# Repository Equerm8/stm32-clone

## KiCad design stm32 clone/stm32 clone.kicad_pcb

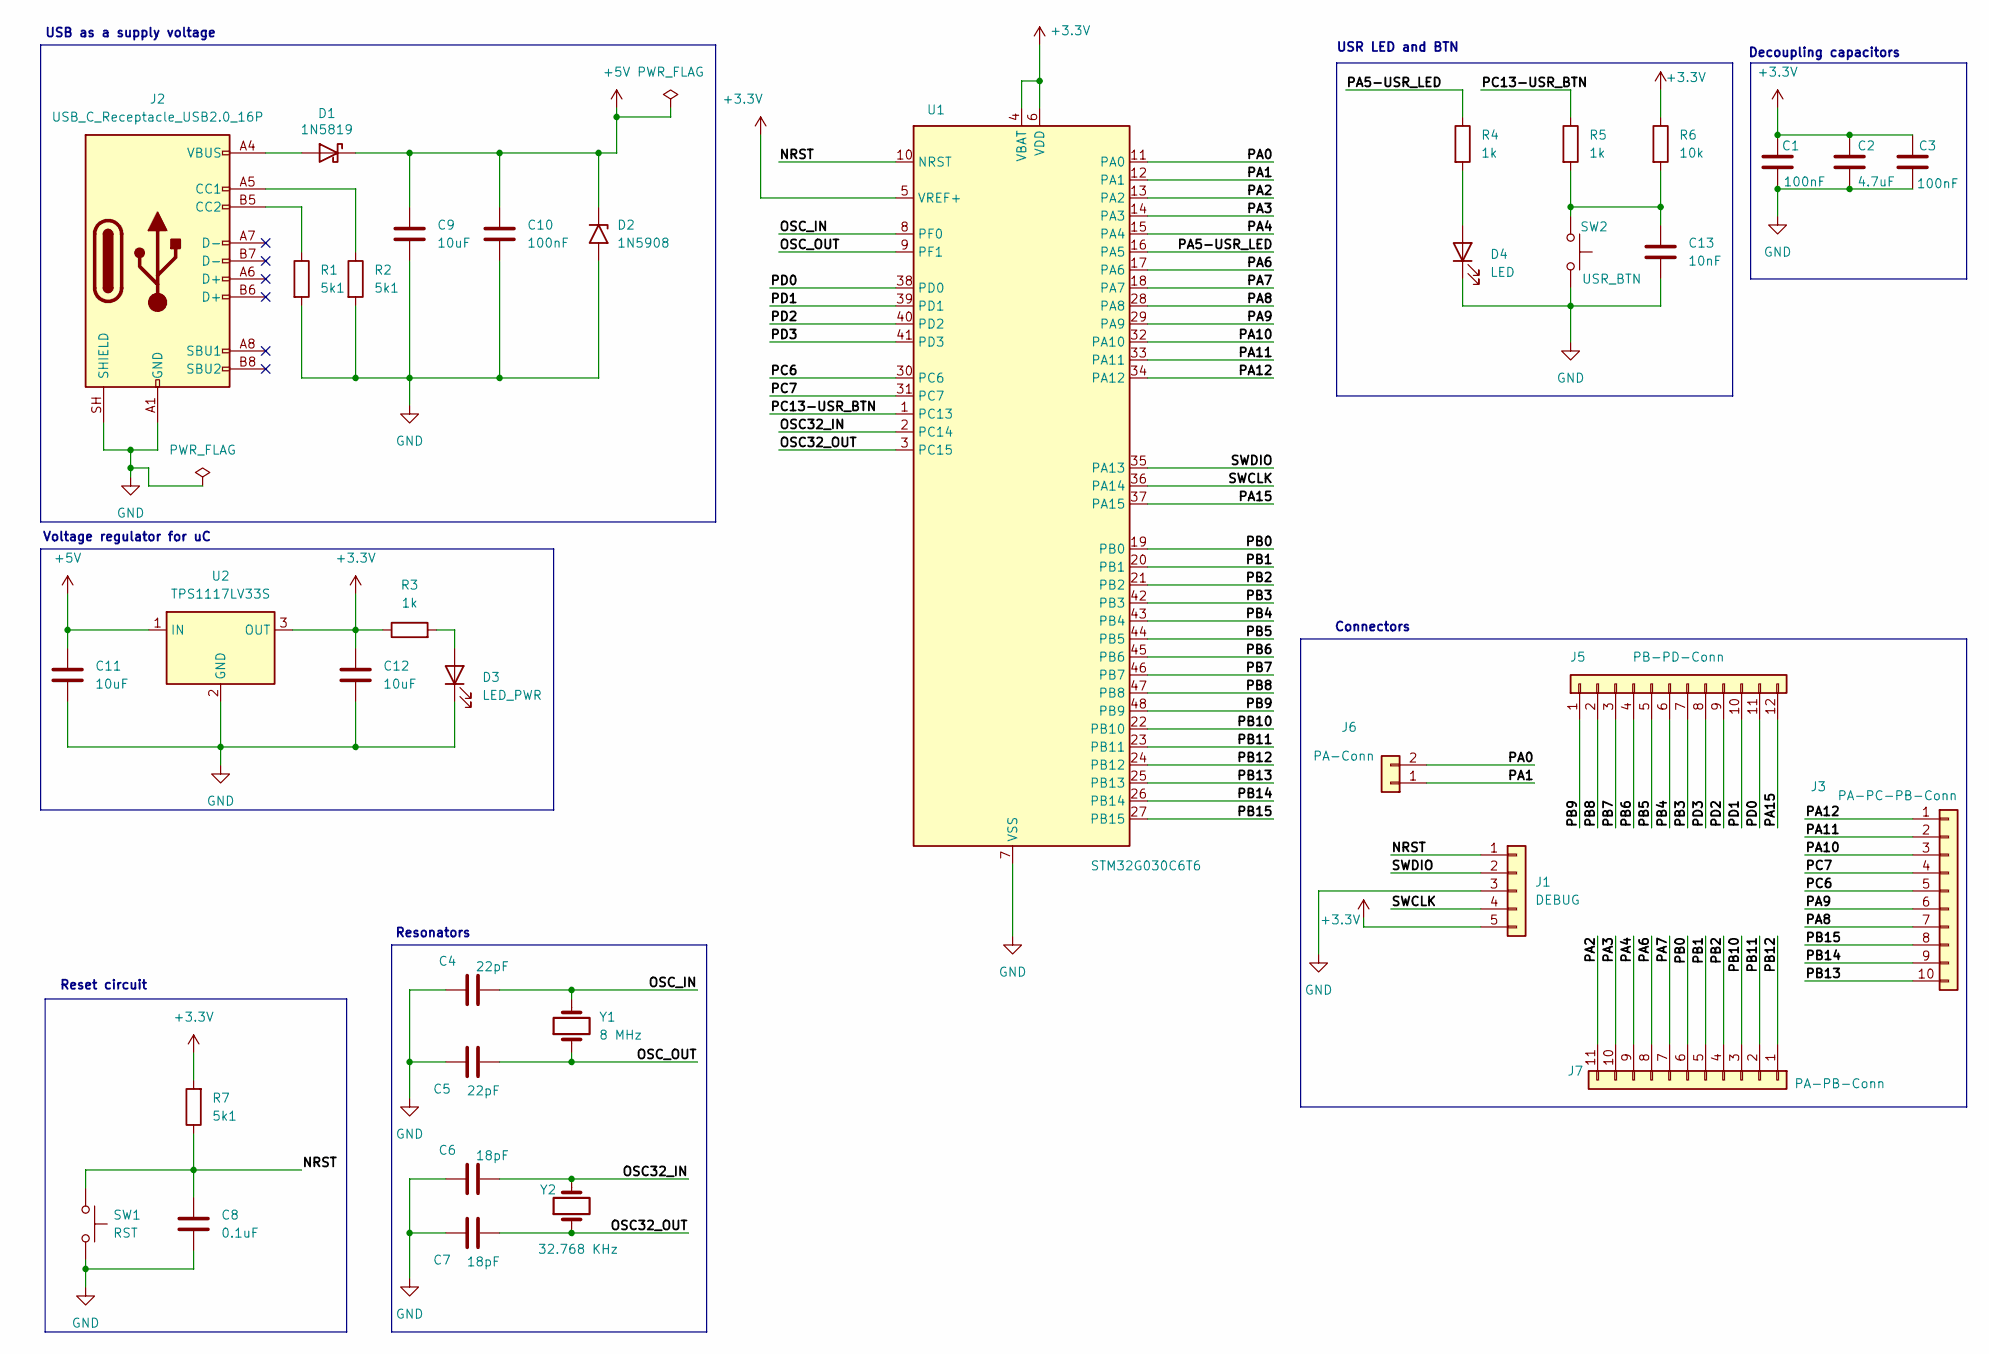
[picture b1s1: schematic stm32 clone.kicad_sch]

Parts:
C1, C3, C10: 100nF; C_0805_2012Metric_Pad1.18x1.45mm_HandSolder
C2: 4.7uF; C_0805_2012Metric_Pad1.18x1.45mm_HandSolder
C4, C5: 22pF; C_0805_2012Metric_Pad1.18x1.45mm_HandSolder
C6, C7: 18pF; C_0805_2012Metric_Pad1.18x1.45mm_HandSolder
C8: 0.1uF; C_0805_2012Metric_Pad1.18x1.45mm_HandSolder
C9, C11, C12: 10uF; C_0805_2012Metric_Pad1.18x1.45mm_HandSolder
C13: 10nF; C_0805_2012Metric_Pad1.18x1.45mm_HandSolder
D1: 1N5819; D_DO-15_P12.70mm_Horizontal
D2: 1N5908; D_DO-201AE_P15.24mm_Horizontal
D3: LED_PWR; LED_D5.0mm
D4: LED; LED_D5.0mm
J1: DEBUG; PinHeader_1x05_P2.54mm_Vertical
J2: USB_C_Receptacle_USB2.0_16P; USB_C_Receptacle_GCT_USB4105-xx-A_16P_TopMnt_Horizontal
J3: PA-PC-PB-Conn; PinHeader_1x10_P2.54mm_Vertical
J5: PB-PD-Conn; PinHeader_1x12_P2.54mm_Vertical
J6: PA-Conn; PinHeader_1x02_P2.54mm_Vertical
J7: PA-PB-Conn; PinHeader_1x11_P2.54mm_Vertical
R1, R2, R7: 5k1; R_0805_2012Metric_Pad1.20x1.40mm_HandSolder
R3, R4, R5: 1k; R_0805_2012Metric_Pad1.20x1.40mm_HandSolder
R6: 10k; R_0805_2012Metric_Pad1.20x1.40mm_HandSolder
SW1: RST; SW_PUSH_6mm_2pin
SW2: USR_BTN; SW_PUSH_6mm_2pin
U1: STM32G030C6T6; LQFP-48_7x7mm_P0.5mm
U2: TPS1117LV33S; SOT-223-3_TabPin2
Y1: 8 MHz; Crystal_HC49-4H_Vertical
Y2: 32.768 KHz; Crystal_C38-LF_D3.0mm_L8.0mm_Vertical

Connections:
+3.3V: C1.1, C2.1, C3.1, C12.1, J1.5, R3.1, R6.1, R7.2, U1.4 (VBAT), U1.5 (VREF+), U1.6 (VDD), U2.3 (OUT)
+5V: C9.1, C10.1, C11.1, D1.1 (K), D2.1 (A1), U2.1 (IN)
/NRST: C8.1, J1.1, R7.1, SW1.1, U1.10 (NRST)
/OSC32_IN: C6.2, U1.2 (PC14), Y2.2
/OSC32_OUT: C7.2, U1.3 (PC15), Y2.1
/OSC_IN: C4.2, U1.8 (PF0), Y1.2
/OSC_OUT: C5.2, U1.9 (PF1), Y1.1
/PA0: J6.2, U1.11 (PA0)
/PA1: J6.1, U1.12 (PA1)
/PA2: J7.11, U1.13 (PA2)
/PA3: J7.10, U1.14 (PA3)
/PA4: J7.9, U1.15 (PA4)
/PA5-USR_LED: R4.1, U1.16 (PA5)
/PA6: J7.8, U1.17 (PA6)
/PA7: J7.7, U1.18 (PA7)
/PA8: J3.7, U1.28 (PA8)
/PA9: J3.6, U1.29 (PA9)
/PA10: J3.3, U1.32 (PA10)
/PA11: J3.2, U1.33 (PA11)
/PA12: J3.1, U1.34 (PA12)
/PA15: J5.12, U1.37 (PA15)
/PB0: J7.6, U1.19 (PB0)
/PB1: J7.5, U1.20 (PB1)
/PB2: J7.4, U1.21 (PB2)
/PB3: J5.7, U1.42 (PB3)
/PB4: J5.6, U1.43 (PB4)
/PB5: J5.5, U1.44 (PB5)
/PB6: J5.4, U1.45 (PB6)
/PB7: J5.3, U1.46 (PB7)
/PB8: J5.2, U1.47 (PB8)
/PB9: J5.1, U1.48 (PB9)
/PB10: J7.3, U1.22 (PB10)
/PB11: J7.2, U1.23 (PB11)
/PB12: J7.1, U1.24 (PB12)
/PB13: J3.10, U1.25 (PB13)
/PB14: J3.9, U1.26 (PB14)
/PB15: J3.8, U1.27 (PB15)
/PC6: J3.5, U1.30 (PC6)
/PC7: J3.4, U1.31 (PC7)
/PC13-USR_BTN: R5.1, U1.1 (PC13)
/PD0: J5.11, U1.38 (PD0)
/PD1: J5.10, U1.39 (PD1)
/PD2: J5.9, U1.40 (PD2)
/PD3: J5.8, U1.41 (PD3)
/SWCLK: J1.4, U1.36 (PA14)
/SWDIO: J1.2, U1.35 (PA13)
GND: C1.2, C2.2, C3.2, C4.1, C5.1, C6.1, C7.1, C8.2, C9.2, C10.2, C11.2, C12.2, C13.2, D2.2 (A2), D3.1 (K), D4.1 (K), J1.3, J2.A1 (GND), J2.A12 (GND), J2.B1 (GND), J2.B12 (GND), J2.SH (SHIELD), R1.2, R2.2, SW1.2, SW2.2, U1.7 (VSS), U2.2 (GND)
unnamed: C13.1, R5.2, R6.2, SW2.1
unnamed: D1.2 (A), J2.A4 (VBUS), J2.A9 (VBUS), J2.B4 (VBUS), J2.B9 (VBUS)
unnamed: D3.2 (A), R3.2
unnamed: D4.2 (A), R4.2
unnamed: J2.A5 (CC1), R2.1
unnamed: J2.B5 (CC2), R1.1

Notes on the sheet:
USR LED and BTN
Decoupling capacitors
Reset circuit
USB as a supply voltage
Resonators
Voltage regulator for uC
Connectors

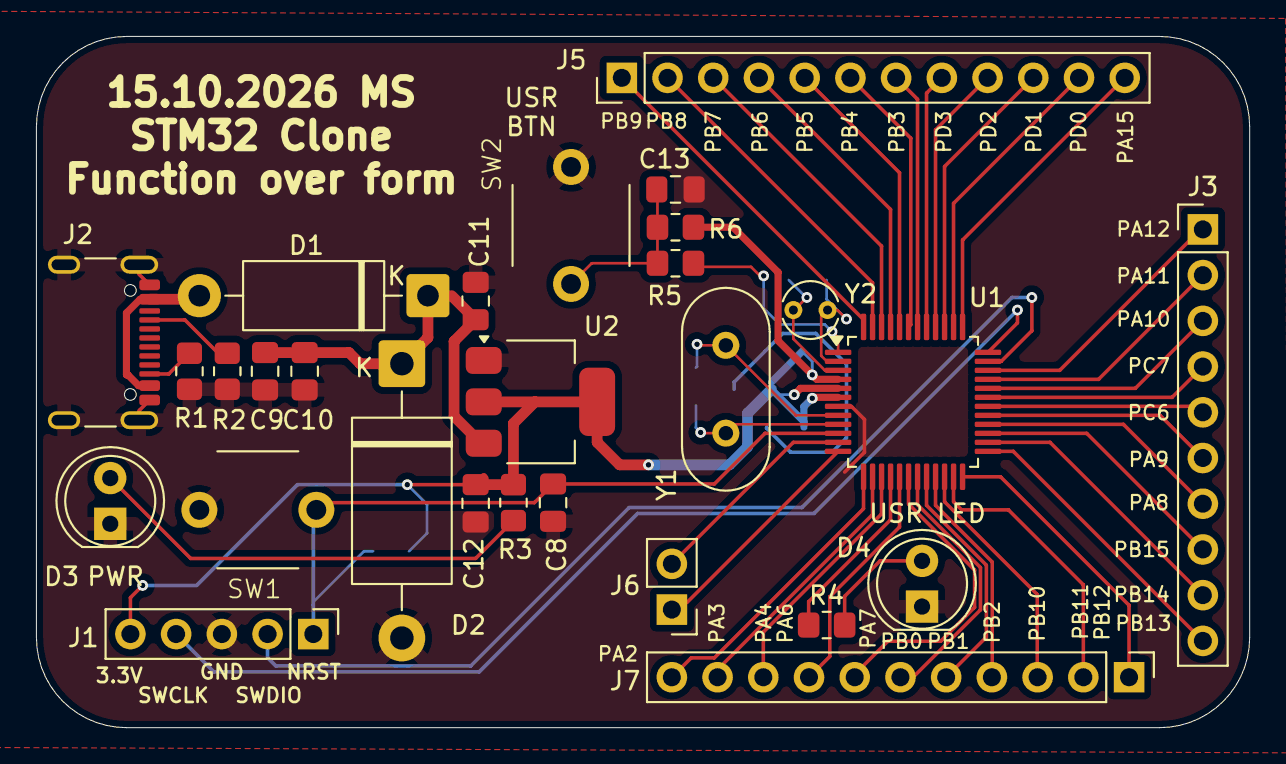
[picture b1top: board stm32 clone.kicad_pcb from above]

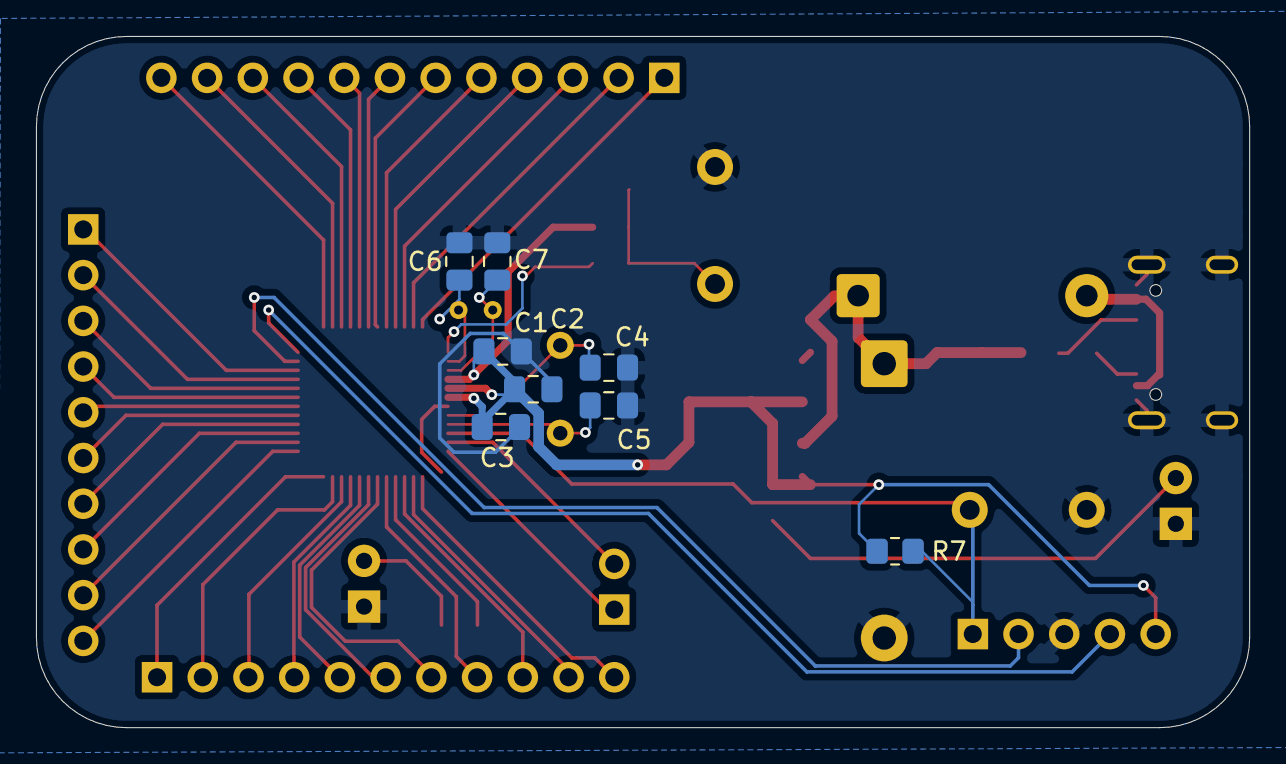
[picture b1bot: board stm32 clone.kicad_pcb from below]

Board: 4 copper layers, 67.4 x 38.4 mm, 36 parts (8 on the bottom side), 53 nets.

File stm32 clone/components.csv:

Cart;Reference;Qty;Value;Footprint;Datasheet;URL
FA£SZ;C1,C3,C19;3;100nF;Capacitor_SMD:C_0805_2012Metric_Pad1.18x1.45mm_HandSolder;;
FA£SZ;C2;1;4.7uF;Capacitor_SMD:C_0805_2012Metric_Pad1.18x1.45mm_HandSolder;;
FA£SZ;C4 C5;2;22pF;Capacitor_SMD:C_0805_2012Metric_Pad1.18x1.45mm_HandSolder;;
FA£SZ;C6, C7;2;18pF;Capacitor_SMD:C_0805_2012Metric_Pad1.18x1.45mm_HandSolder;;
FA£SZ;C8;1;0.1uF;Capacitor_SMD:C_0805_2012Metric_Pad1.18x1.45mm_HandSolder;;
FA£SZ;C9, C11, C12;3;10uF;Capacitor_SMD:C_0805_2012Metric_Pad1.18x1.45mm_HandSolder;;
FA£SZ;C13;1;10nF;Capacitor_SMD:C_0805_2012Metric_Pad1.18x1.45mm_HandSolder;;
FA£SZ;D1;1;1N5819;Diode_THT:D_DO-15_P12.70mm_Horizontal;https://www.tme.eu/Document/7e78c56f041fe00f7158152d6ddb2c6e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;https://www.tme.eu/pl/details/1n5819-dio/diody-schottky-tht/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
FA£SZ;D2;1;1N5908;Diode_THT:D_DO-201AE_P15.24mm_Horizontal;https://www.tme.eu/Document/b573c1072669355e40bbb17bb3e94432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;https://www.tme.eu/pl/details/1n5908/diody-tvs-tht-jednokier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
FA£SZ;D3;1;LED_PWR;LED_THT:LED_D5.0mm;;
FA£SZ;D4;1;LED;LED_THT:LED_D5.0mm;;
FA£SZ;J1;1;DEBUG;Connector_PinHeader_2.54mm:PinHeader_1x05_P2.54mm_Vertical;;
FA£SZ;J2;1;USB_C_Receptacle_USB2.0_16P;Connector_USB:USB_C_Receptacle_GCT_USB4105-xx-A_16P_TopMnt_Horizontal;https://www.usb.org/sites/default/files/documents/usb_type-c.zip;
FA£SZ;J3;1;PA-PC-PB-Conn;Connector_PinHeader_2.54mm:PinHeader_1x10_P2.54mm_Vertical;;
FA£SZ;J5;1;PB-PD-Conn;Connector_PinHeader_2.54mm:PinHeader_1x12_P2.54mm_Vertical;;
FA£SZ;J6;1;PA-Conn;Connector_PinHeader_2.54mm:PinHeader_1x02_P2.54mm_Vertical;;
FA£SZ;J7;1;PA-PB-Conn;Connector_PinHeader_2.54mm:PinHeader_1x11_P2.54mm_Vertical;;
FA£SZ;R1,R2;2;5k1;Resistor_SMD:R_0805_2012Metric_Pad1.20x1.40mm_HandSolder;;
FA£SZ;R3,R4,R5;3;1k;Resistor_SMD:R_0805_2012Metric_Pad1.20x1.40mm_HandSolder;;
FA£SZ;R6;1;10k;Resistor_SMD:R_0805_2012Metric_Pad1.20x1.40mm_HandSolder;;
FA£SZ;SW1;1;RST;Button_Switch_THT:SW_PUSH_6mm_2pin;;
FA£SZ;SW2;1;USR_BTN;Button_Switch_THT:SW_PUSH_6mm_2pin;;
FA£SZ;U1;1;STM32G030C6T6;Package_QFP:LQFP-48_7x7mm_P0.5mm;https://www.st.com/resource/en/datasheet/stm32g030c6.pdf;https://www.tme.eu/pl/details/stm32g030c6t6/mikrokontrolery-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
FA£SZ;U2;1;TPS1117LV33S;Package_TO_SOT_SMD:SOT-223-3_TabPin2;https://www.tme.eu/Document/4bc160b374101d59d8b6409d0be1e024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;TPS1117LV33S
FA£SZ;Y1;1;8 MHz;Crystal:Crystal_HC49-4H_Vertical;https://botland.com.pl/index.php?controller=attachment&id_at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;https://botland.com.pl/rezonatory/167-rezonator-kwarcowy-8mh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
FA£SZ;Y2;1;32.768 KHz;Crystal:Crystal_C38-LF_D3.0mm_L8.0mm_Vertical;https://www.piekarz.pl/pdf/1911/;https://www.piekarz.pl/09670-rezonator-kwarcowy-32-768khz-fi-3x8mm/

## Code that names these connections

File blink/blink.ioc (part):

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Mcu.Name=STM32G030C(6-8)Tx
Mcu.Package=LQFP48
Mcu.UserName=STM32G030C6Tx
PA5.GPIOParameters=GPIO_Label
PA5.GPIO_Label=USR_LED
PA5.Signal=GPIO_Output
PC14-OSC32_IN\ (PC14).Mode=LSE-External-Oscillator
PC14-OSC32_IN\ (PC14).Signal=RCC_OSC32_IN
PC15-OSC32_OUT\ (PC15).Mode=LSE-External-Oscillator
PC15-OSC32_OUT\ (PC15).Signal=RCC_OSC32_OUT
RCC.HSE_VALUE=8000000
RCC.SYSCLKFreq_VALUE=16000000
board=custom
